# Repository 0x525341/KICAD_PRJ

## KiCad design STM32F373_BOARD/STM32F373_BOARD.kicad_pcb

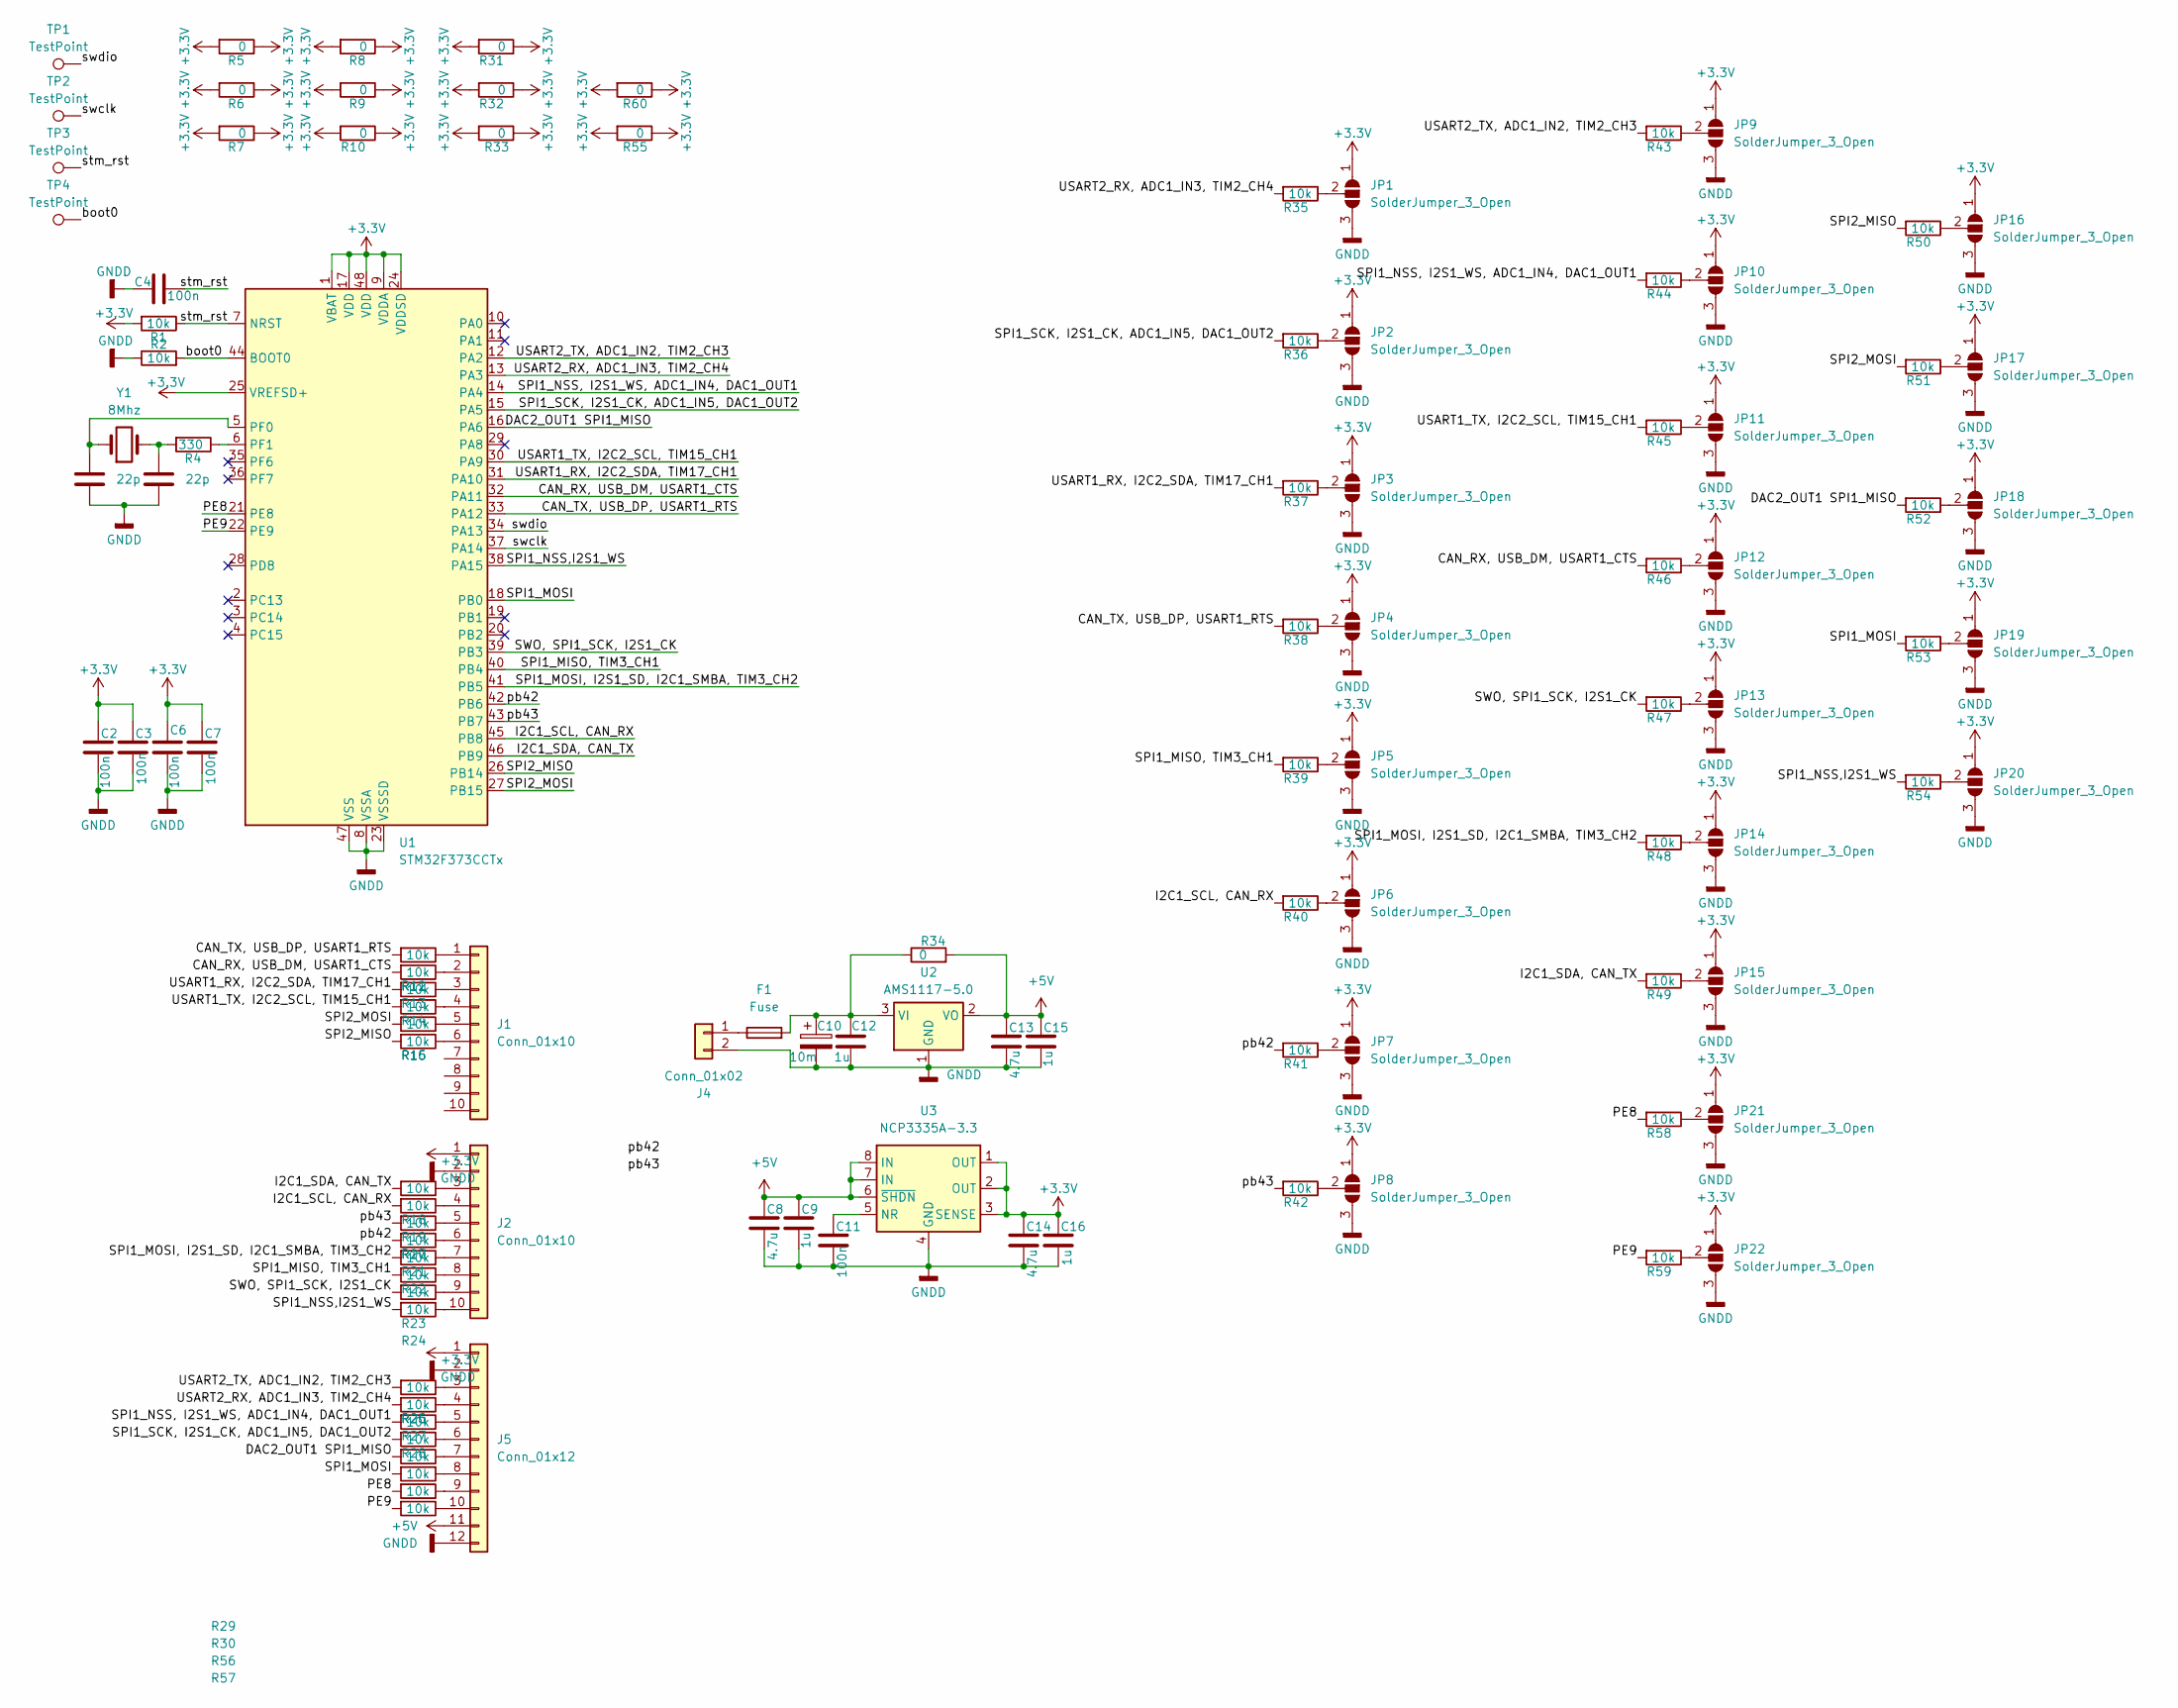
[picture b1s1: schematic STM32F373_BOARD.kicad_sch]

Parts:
C1, C5: 22p; C_0805_2012Metric
C2, C3, C4, C6, C7, C11: 100n; C_0805_2012Metric
C8, C13, C14: 4.7u; C_1206_3216Metric
C9, C12, C15, C16: 1u; C_1206_3216Metric
C10: 10m; CP_EIA-7343-31_Kemet-D_HandSolder
F1: Fuse; Fuse_1210_3225Metric_Pad1.42x2.65mm_HandSolder
J1, J2: Conn_01x10; PinHeader_1x10_P2.54mm_Vertical_SMD_Pin1Right
J4: Conn_01x02; PinSocket_1x02_P2.54mm_Vertical_SMD_Pin1Right
J5: Conn_01x12; PinHeader_1x12_P2.54mm_Vertical_SMD_Pin1Left
JP1, JP2, JP3, JP4, JP5, JP6, JP7, JP8, JP9, JP10, JP11, JP12, JP13, JP14, JP15, JP16, JP17, JP18, JP19, JP20, JP21, JP22: SolderJumper_3_Open; SolderJumper-3_P1.3mm_Open_RoundedPad1.0x1.5mm
R1: 10k; R_0805_2012Metric
R2, R11, R12, R13, R14, R15, R16, R17, R18, R19, R20, R21, R22, R23, R24, R25, R26, R27, R28, R29, R30, R35, R36, R37, R38, R39, R40, R41, R42, R43, R44, R45, R46, R47, R48, R49, R50, R51, R52, R53, R54, R56, R57, R58, R59: 10k; R_1206_3216Metric
R4: 330; R_0805_2012Metric
R5, R6, R7, R8, R9, R10, R31, R32, R33, R55, R60: 0; R_0805_2012Metric
R34: 0; R_1206_3216Metric
TP1, TP2, TP3, TP4: TestPoint; TestPoint_Pad_1.5x1.5mm
U1: STM32F373CCTx; LQFP-48_7x7mm_P0.5mm
U2: AMS1117-5.0; SOT-223-3_TabPin2
U3: NCP3335A-3.3; MSOP-8_3x3mm_P0.65mm
Y1: 8Mhz; Crystal_SMD_0603-2Pin_6.0x3.5mm

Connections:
+3.3V: C2.1, C3.1, C6.1, C7.1, C14.1, C16.1, J2.1, J5.1, JP1.1 (A), JP2.1 (A), JP3.1 (A), JP4.1 (A), JP5.1 (A), JP6.1 (A), JP7.1 (A), JP8.1 (A), JP9.1 (A), JP10.1 (A), JP11.1 (A), JP12.1 (A), JP13.1 (A), JP14.1 (A), JP15.1 (A), JP16.1 (A), JP17.1 (A), JP18.1 (A), JP19.1 (A), JP20.1 (A), JP21.1 (A), JP22.1 (A), R1.2, R5.1, R5.2, R6.1, R6.2, R7.1, R7.2, R8.1, R8.2, R9.1, R9.2, R10.1, R10.2, R31.1, R31.2, R32.1, R32.2, R33.1, R33.2, R55.1, R55.2, R60.1, R60.2, U1.1 (VBAT), U1.9 (VDDA), U1.17 (VDD), U1.24 (VDDSD), U1.25 (VREFSD+), U1.48 (VDD), U3.1 (OUT), U3.2 (OUT), U3.3 (SENSE)
+5V: C8.1, C9.1, C13.1, C15.1, J5.11, R34.2, U2.2 (VO), U3.6 (~SHDN), U3.7 (IN), U3.8 (IN)
/CAN_RX, USB_DM, USART1_CTS: R12.2, R46.2, U1.32 (PA11)
/CAN_TX, USB_DP, USART1_RTS: R11.2, R38.2, U1.33 (PA12)
/DAC2_OUT1 SPI1_MISO: R29.2, R52.2, U1.16 (PA6)
/I2C1_SCL, CAN_RX: R18.2, R40.2, U1.45 (PB8)
/I2C1_SDA, CAN_TX: R17.2, R49.2, U1.46 (PB9)
/PE8: R56.2, R58.2, U1.21 (PE8)
/PE9: R57.2, R59.2, U1.22 (PE9)
/SPI1_MISO, TIM3_CH1: R22.2, R39.2, U1.40 (PB4)
/SPI1_MOSI: R30.2, R53.2, U1.18 (PB0)
/SPI1_MOSI, I2S1_SD, I2C1_SMBA, TIM3_CH2: R21.2, R48.2, U1.41 (PB5)
/SPI1_NSS, I2S1_WS, ADC1_IN4, DAC1_OUT1: R27.2, R44.2, U1.14 (PA4)
/SPI1_NSS,I2S1_WS: R24.2, R54.2, U1.38 (PA15)
/SPI1_SCK, I2S1_CK, ADC1_IN5, DAC1_OUT2: R28.2, R36.2, U1.15 (PA5)
/SPI2_MISO: R16.2, R50.2, U1.26 (PB14)
/SPI2_MOSI: R15.2, R51.2, U1.27 (PB15)
/SWO, SPI1_SCK, I2S1_CK: R23.2, R47.2, U1.39 (PB3)
/USART1_RX, I2C2_SDA, TIM17_CH1: R13.2, R37.2, U1.31 (PA10)
/USART1_TX, I2C2_SCL, TIM15_CH1: R14.2, R45.2, U1.30 (PA9)
/USART2_RX, ADC1_IN3, TIM2_CH4: R26.2, R35.2, U1.13 (PA3)
/USART2_TX, ADC1_IN2, TIM2_CH3: R25.2, R43.2, U1.12 (PA2)
/boot0: R2.2, TP4.1 (1_1), U1.44 (BOOT0)
/pb42: R20.2, R41.2, U1.42 (PB6)
/pb43: R19.2, R42.2, U1.43 (PB7)
/stm_rst: C4.2, R1.1, TP3.1 (1_1), U1.7 (NRST)
/swclk: TP2.1 (1_1), U1.37 (PA14)
/swdio: TP1.1 (1_1), U1.34 (PA13)
GNDD: C1.2, C2.2, C3.2, C4.1, C5.2, C6.2, C7.2, C8.2, C9.2, C10.2, C11.2, C12.2, C13.2, C14.2, C15.2, C16.2, J2.2, J4.2, J5.2, J5.12, JP1.3 (B), JP2.3 (B), JP3.3 (B), JP4.3 (B), JP5.3 (B), JP6.3 (B), JP7.3 (B), JP8.3 (B), JP9.3 (B), JP10.3 (B), JP11.3 (B), JP12.3 (B), JP13.3 (B), JP14.3 (B), JP15.3 (B), JP16.3 (B), JP17.3 (B), JP18.3 (B), JP19.3 (B), JP20.3 (B), JP21.3 (B), JP22.3 (B), R2.1, U1.8 (VSSA), U1.23 (VSSSD), U1.47 (VSS), U2.1 (GND), U3.4 (GND)
unnamed: C5.1, R4.2, Y1.2
unnamed: J1.1, R11.1
unnamed: J1.2, R12.1
unnamed: J1.3, R13.1
unnamed: J1.4, R14.1
unnamed: J1.5, R15.1
unnamed: J1.6, R16.1
unnamed: J2.3, R17.1
unnamed: J2.4, R18.1
unnamed: J2.5, R19.1
unnamed: J2.6, R20.1
unnamed: J2.7, R21.1
unnamed: J2.8, R22.1
unnamed: J2.9, R23.1
unnamed: J2.10, R24.1
unnamed: F1.1, J4.1
unnamed: J5.3, R25.1
unnamed: J5.4, R26.1
unnamed: J5.5, R27.1
unnamed: J5.6, R28.1
unnamed: J5.7, R29.1
unnamed: J5.8, R30.1
unnamed: J5.9, R56.1
unnamed: J5.10, R57.1
unnamed: JP1.2 (C), R35.1
unnamed: JP2.2 (C), R36.1
unnamed: JP3.2 (C), R37.1
unnamed: JP4.2 (C), R38.1
unnamed: JP5.2 (C), R39.1
unnamed: JP6.2 (C), R40.1
unnamed: JP7.2 (C), R41.1
unnamed: JP8.2 (C), R42.1
unnamed: JP9.2 (C), R43.1
unnamed: JP10.2 (C), R44.1
unnamed: JP11.2 (C), R45.1
unnamed: JP12.2 (C), R46.1
unnamed: JP13.2 (C), R47.1
unnamed: JP14.2 (C), R48.1
unnamed: JP15.2 (C), R49.1
unnamed: JP16.2 (C), R50.1
unnamed: JP17.2 (C), R51.1
unnamed: JP18.2 (C), R52.1
unnamed: JP19.2 (C), R53.1
unnamed: JP20.2 (C), R54.1
unnamed: JP21.2 (C), R58.1
unnamed: JP22.2 (C), R59.1
unnamed: C1.1, U1.5 (PF0), Y1.1
unnamed: R4.1, U1.6 (PF1)
unnamed: C10.1, C12.1, F1.2, R34.1, U2.3 (VI)
unnamed: C11.1, U3.5 (NR)

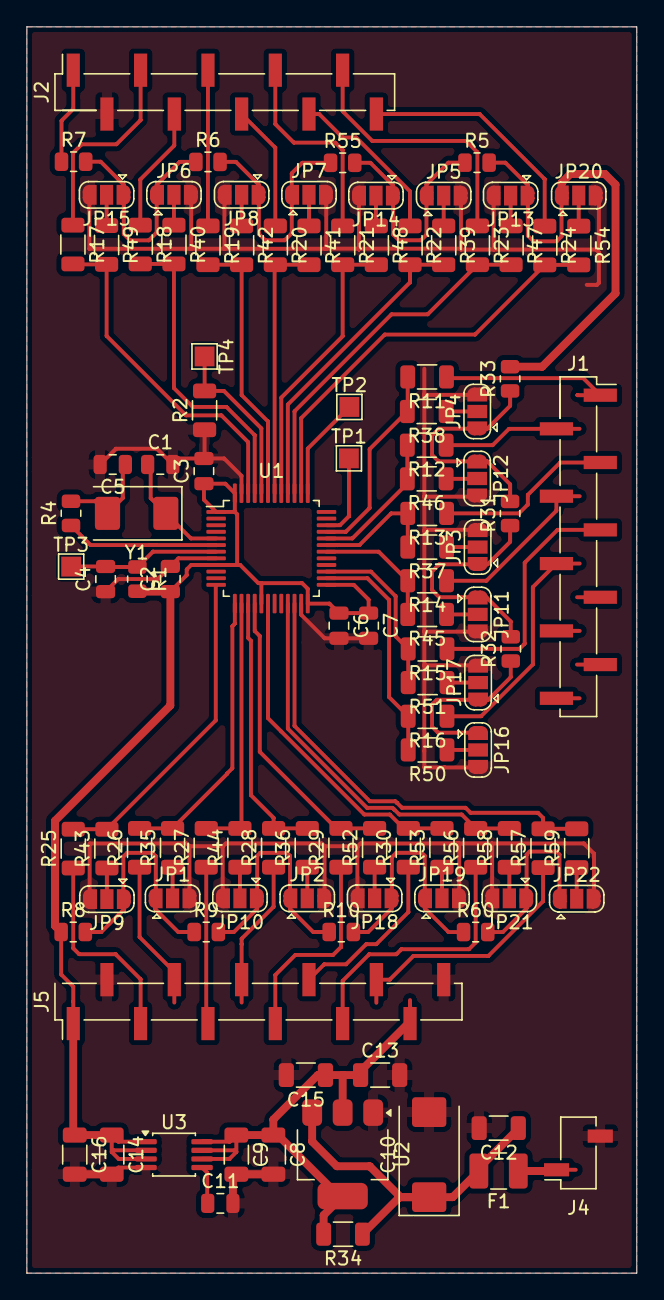
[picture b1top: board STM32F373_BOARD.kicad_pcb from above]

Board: 2 copper layers, 46.0 x 94.0 mm, 110 parts (0 on the bottom side), 79 nets.

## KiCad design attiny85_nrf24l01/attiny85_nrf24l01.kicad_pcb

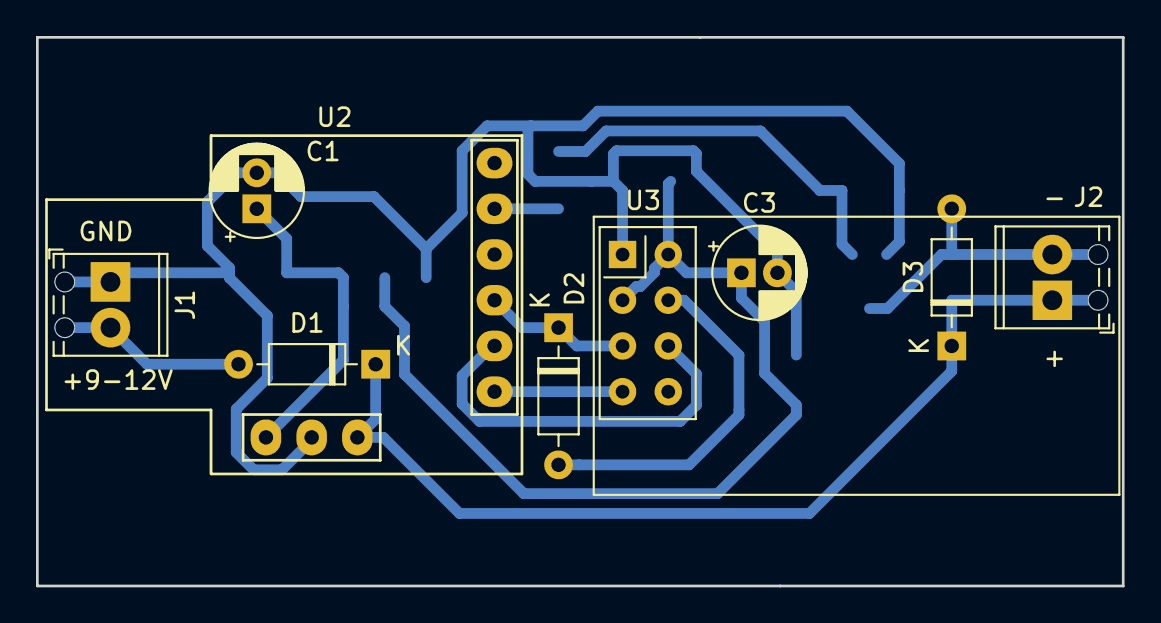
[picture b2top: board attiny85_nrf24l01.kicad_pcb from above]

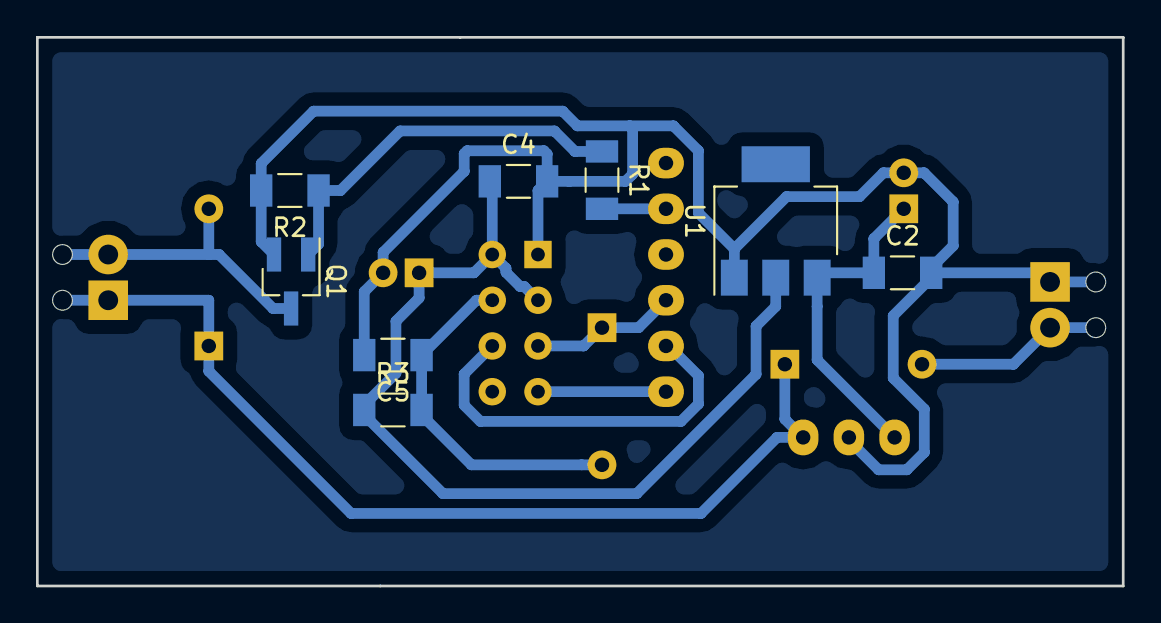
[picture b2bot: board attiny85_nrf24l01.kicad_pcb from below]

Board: 2 copper layers, 60.3 x 30.5 mm, 17 parts (8 on the bottom side), 12 nets.

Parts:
C1, C3: 10mkF; CP_Radial_D5.0mm_P2.00mm
C2, C4: 0,1mkF; C_1206_3216Metric_Pad1.24x1.80mm_HandSolder
C5: 10/100nF; C_1206_3216Metric_Pad1.24x1.80mm_HandSolder
D1: 1N5819; D_DO-35_SOD27_P7.62mm_Horizontal
D2: 4148; D_DO-35_SOD27_P7.62mm_Horizontal
D3: 1N4007; D_DO-35_SOD27_P7.62mm_Horizontal
J1: POWER; TerminalBlock_Phoenix_MPT-0,5-2-2.54_1x02_P2.54mm_Horizontal
J2: VALVE; TerminalBlock_Phoenix_MPT-0,5-2-2.54_1x02_P2.54mm_Horizontal
Q1: IRLML2502TRPBF; SOT-23_Handsoldering
R1: 100Om; R_1206_3216Metric_Pad1.24x1.80mm_HandSolder
R2: 10kOm; R_1206_3216Metric_Pad1.24x1.80mm_HandSolder
R3: 1/22kOm; R_1206_3216Metric_Pad1.24x1.80mm_HandSolder
U1: LT1117-3.3; SOT-223
U2: DIGISPARK; Shield_Digispark
U3: NRF24L01_Breakout; nRF24L01_Breakout

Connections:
+9V: D1.1, D3.1, J2.1, U2.8
+BATT: D1.2, J1.2
-BATT: C1.2, C2.2, C3.2, C4.2, C5.2, J1.1, Q1.2, R2.2, U1.1, U2.4, U3.1
/+3,3V: C3.1, C4.1, R3.1, U1.2, U3.2, U3.3
/+5V: C1.1, C2.1, U1.3, U2.9
/CONTROL_VALVE: R1.2, U2.3
unnamed: C5.1, D2.2, R3.2, U3.4
unnamed: D2.1, U2.7, U3.5
unnamed: D3.2, J2.2, Q1.3
unnamed: Q1.1, R1.1, R2.1
unnamed: U2.5, U3.7
unnamed: U2.6, U3.6

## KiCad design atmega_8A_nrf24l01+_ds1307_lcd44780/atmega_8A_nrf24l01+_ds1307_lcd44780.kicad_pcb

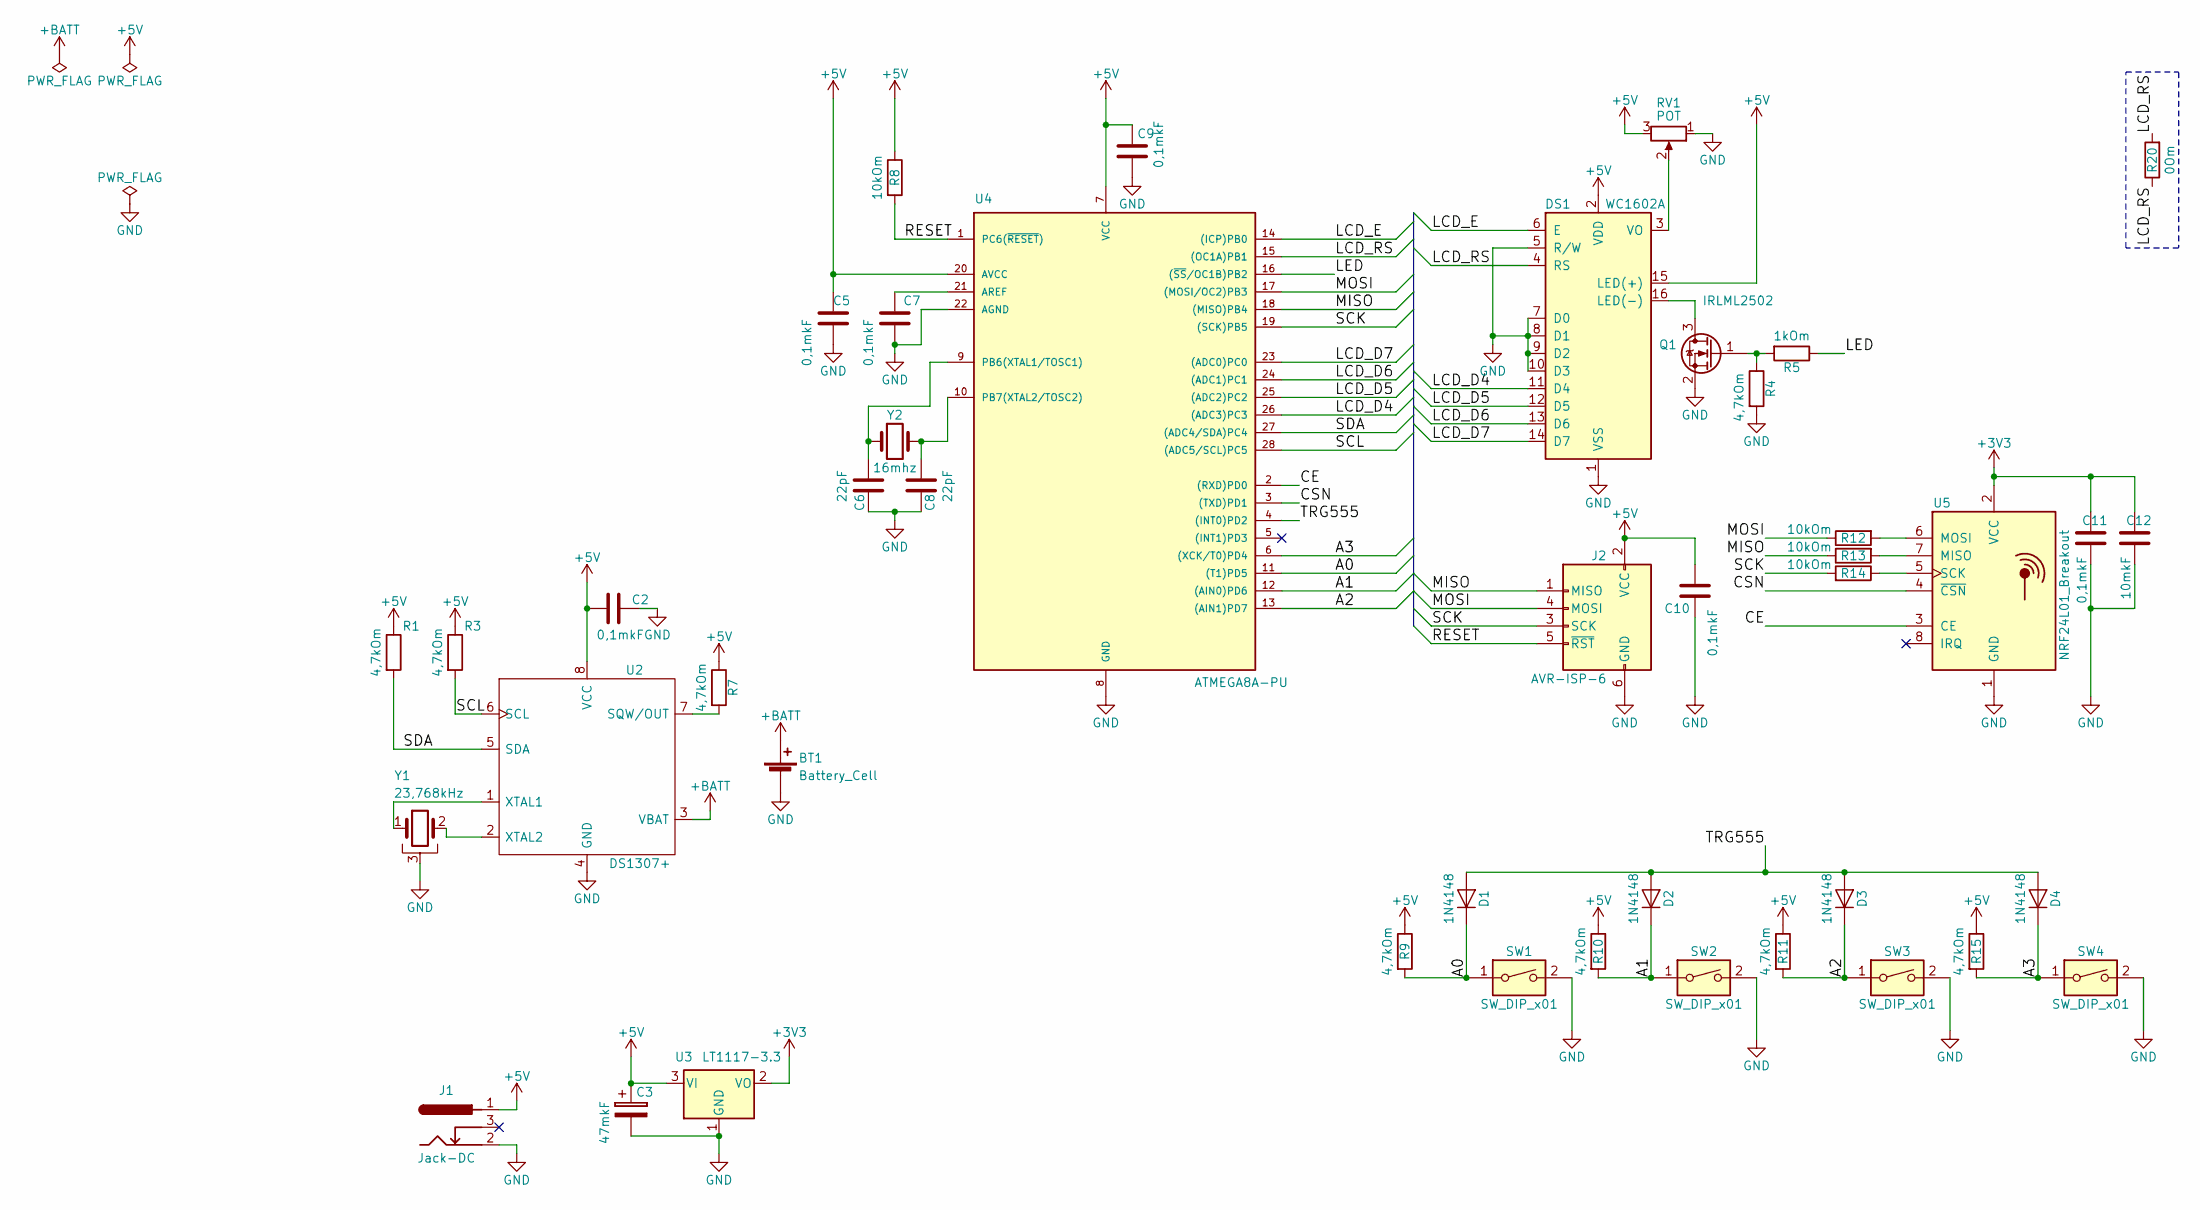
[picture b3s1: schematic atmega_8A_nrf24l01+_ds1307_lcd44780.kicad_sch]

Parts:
BT1: Battery_Cell; BatteryHolder_CR2032H
C2, C5, C7, C9, C10, C11: 0,1mkF; C_1206_3216Metric_Pad1.24x1.80mm_HandSolder
C3: 47mkF; CP_Radial_D5.0mm_P2.00mm
C6, C8: 22pF; C_1206_3216Metric_Pad1.24x1.80mm_HandSolder
C12: 10mkF; C_1206_3216Metric_Pad1.24x1.80mm_HandSolder
D1, D2, D3, D4: 1N4148; D_DO-35_SOD27_P7.62mm_Horizontal
DS1: WC1602A
J1: Jack-DC; ds-313
J2: AVR-ISP-6; PinHeader_2x03_P2.54mm_Vertical
Q1: IRLML2502; SOT-23_Handsoldering
R1, R3, R4, R7, R9, R10, R11, R15: 4,7kOm; R_1206_3216Metric_Pad1.24x1.80mm_HandSolder
R5: 1kOm; R_1206_3216Metric_Pad1.24x1.80mm_HandSolder
R8, R12, R13, R14: 10kOm; R_1206_3216Metric_Pad1.24x1.80mm_HandSolder
R20: 0Om; R_1206_3216Metric_Pad1.24x1.80mm_HandSolder
RV1: POT; Potentiometer_ACP_CA9-H5_Horizontal
SW1, SW2, SW3, SW4: SW_DIP_x01; SW_PUSH_6mm
U2: DS1307+; SOIC-8_3.9x4.9mm_P1.27mm
U3: LT1117-3.3; SOT-223-3_TabPin2
U4: ATMEGA8A-PU; DIP-28_W7.62mm_LongPads
U5: NRF24L01_Breakout; nRF24L01_Breakout
Y1: 23,768kHz; Crystal_AT310_D3.0mm_L10.0mm_Horizontal_1EP_style2
Y2: 16mhz; Crystal_HC49-4H_Vertical

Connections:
+3V3: C11.2, C12.2, U3.2 (VO), U5.2 (VCC)
+5V: C2.2, C3.1, C5.2, C9.1, C10.2, DS1.2 (VDD), DS1.15 (LED(+)), J1.1, J2.2 (VCC), R1.1, R3.1, R7.1, R8.1, R9.1, R10.1, R11.1, R15.1, RV1.3, U2.8 (VCC), U3.3 (VI), U4.7 (VCC), U4.20 (AVCC)
+BATT: BT1.1 (+), U2.3 (VBAT)
/A0: D1.1 (K), R9.2, SW1.1, U4.11 ((T1)PD5)
/A1: D2.1 (K), R10.2, SW2.1, U4.12 ((AIN0)PD6)
/A2: D3.1 (K), R11.2, SW3.1, U4.13 ((AIN1)PD7)
/A3: D4.1 (K), R15.2, SW4.1, U4.6 ((XCK/T0)PD4)
/CE: U4.2 ((RXD)PD0), U5.3 (CE)
/CSN: U4.3 ((TXD)PD1), U5.4 (~CSN)
/LCD_D4: DS1.11 (D4), U4.26 ((ADC3)PC3)
/LCD_D5: DS1.12 (D5), U4.25 ((ADC2)PC2)
/LCD_D6: DS1.13 (D6), U4.24 ((ADC1)PC1)
/LCD_D7: DS1.14 (D7), U4.23 ((ADC0)PC0)
/LCD_E: DS1.6 (E), U4.14 ((ICP)PB0)
/LCD_RS: DS1.4 (RS), R20.1, R20.2, U4.15 ((OC1A)PB1)
/LED: R5.1, U4.16 ((~SS/OC1B)PB2)
/MISO: J2.1 (MISO), R13.1, U4.18 ((MISO)PB4)
/MOSI: J2.4 (MOSI), R12.1, U4.17 ((MOSI/OC2)PB3)
/RESET: J2.5 (~RST), R8.2, U4.1 (PC6(~RESET))
/SCK: J2.3 (SCK), R14.2, U4.19 ((SCK)PB5)
/SCL: R3.2, U2.6 (SCL), U4.28 ((ADC5/SCL)PC5)
/SDA: R1.2, U2.5 (SDA), U4.27 ((ADC4/SDA)PC4)
/TRG555: D1.2 (A), D2.2 (A), D3.2 (A), D4.2 (A), U4.4 ((INT0)PD2)
GND: BT1.2 (-), C2.1, C3.2, C5.1, C6.2, C7.1, C8.2, C9.2, C10.1, C11.1, C12.1, DS1.1 (VSS), DS1.5 (R/W), DS1.7 (D0), DS1.8 (D1), DS1.9 (D2), DS1.10 (D3), J1.2, J2.6 (GND), Q1.2 (S), R4.2, RV1.1, SW1.2, SW2.2, SW3.2, SW4.2, U2.4 (GND), U3.1 (GND), U4.8 (GND), U4.22 (AGND), U5.1 (GND), Y1.3
unnamed: C6.1, U4.9 (PB6(XTAL1/TOSC1)), Y2.1
unnamed: C7.2, U4.21 (AREF)
unnamed: C8.1, U4.10 (PB7(XTAL2/TOSC2)), Y2.2
unnamed: DS1.3 (VO), RV1.2
unnamed: DS1.16 (LED(-)), Q1.3 (D)
unnamed: Q1.1 (G), R4.1, R5.2
unnamed: R7.2, U2.7 (SQW/OUT)
unnamed: R12.2, U5.6 (MOSI)
unnamed: R13.2, U5.7 (MISO)
unnamed: R14.1, U5.5 (SCK)
unnamed: U2.1 (XTAL1), Y1.1
unnamed: U2.2 (XTAL2), Y1.2

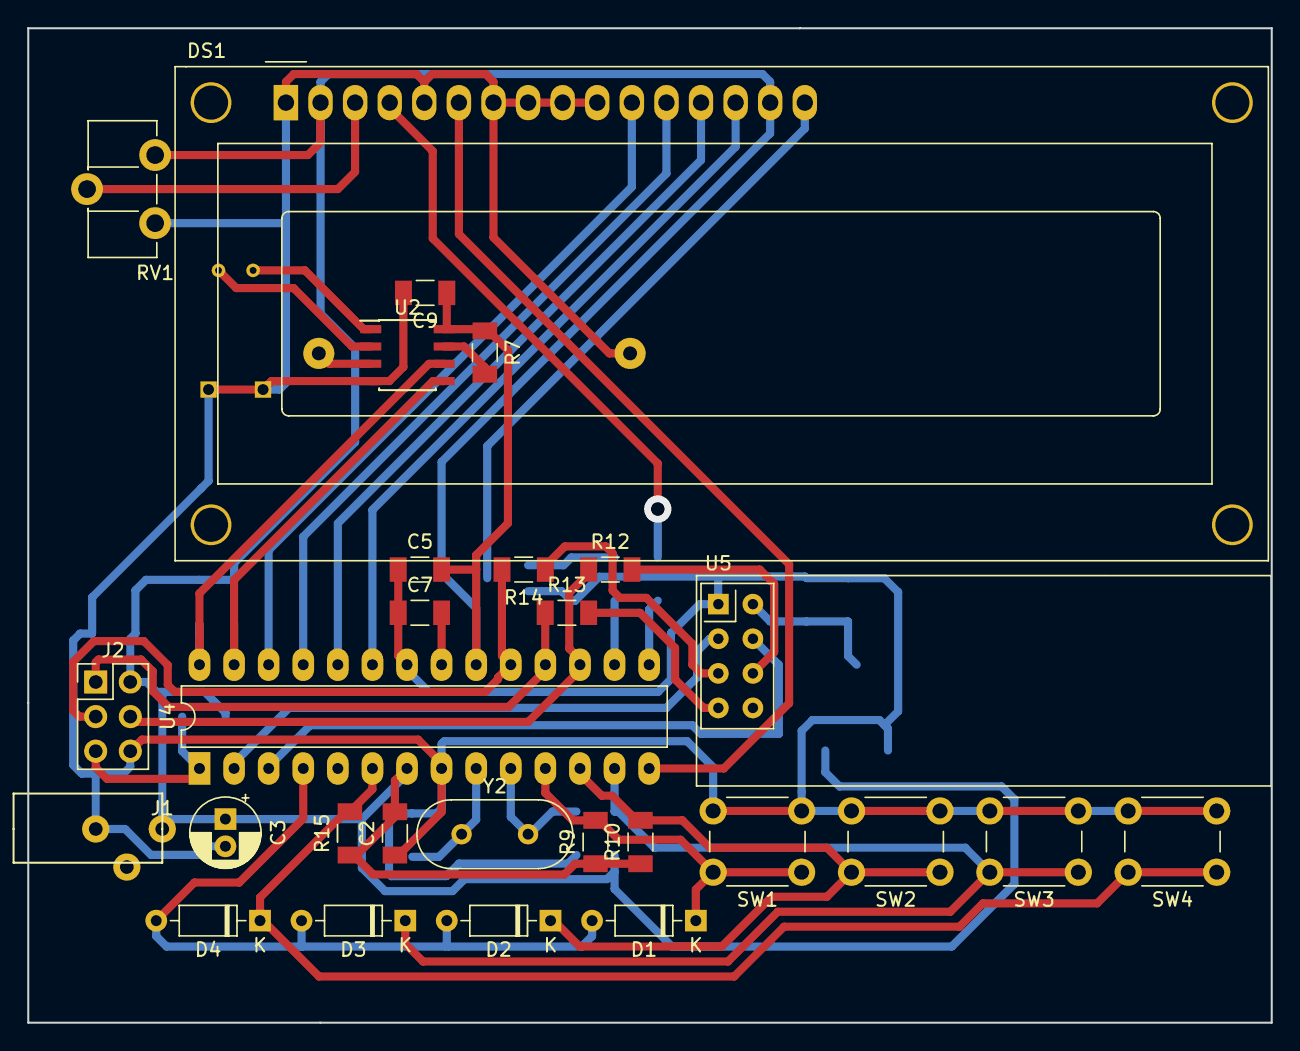
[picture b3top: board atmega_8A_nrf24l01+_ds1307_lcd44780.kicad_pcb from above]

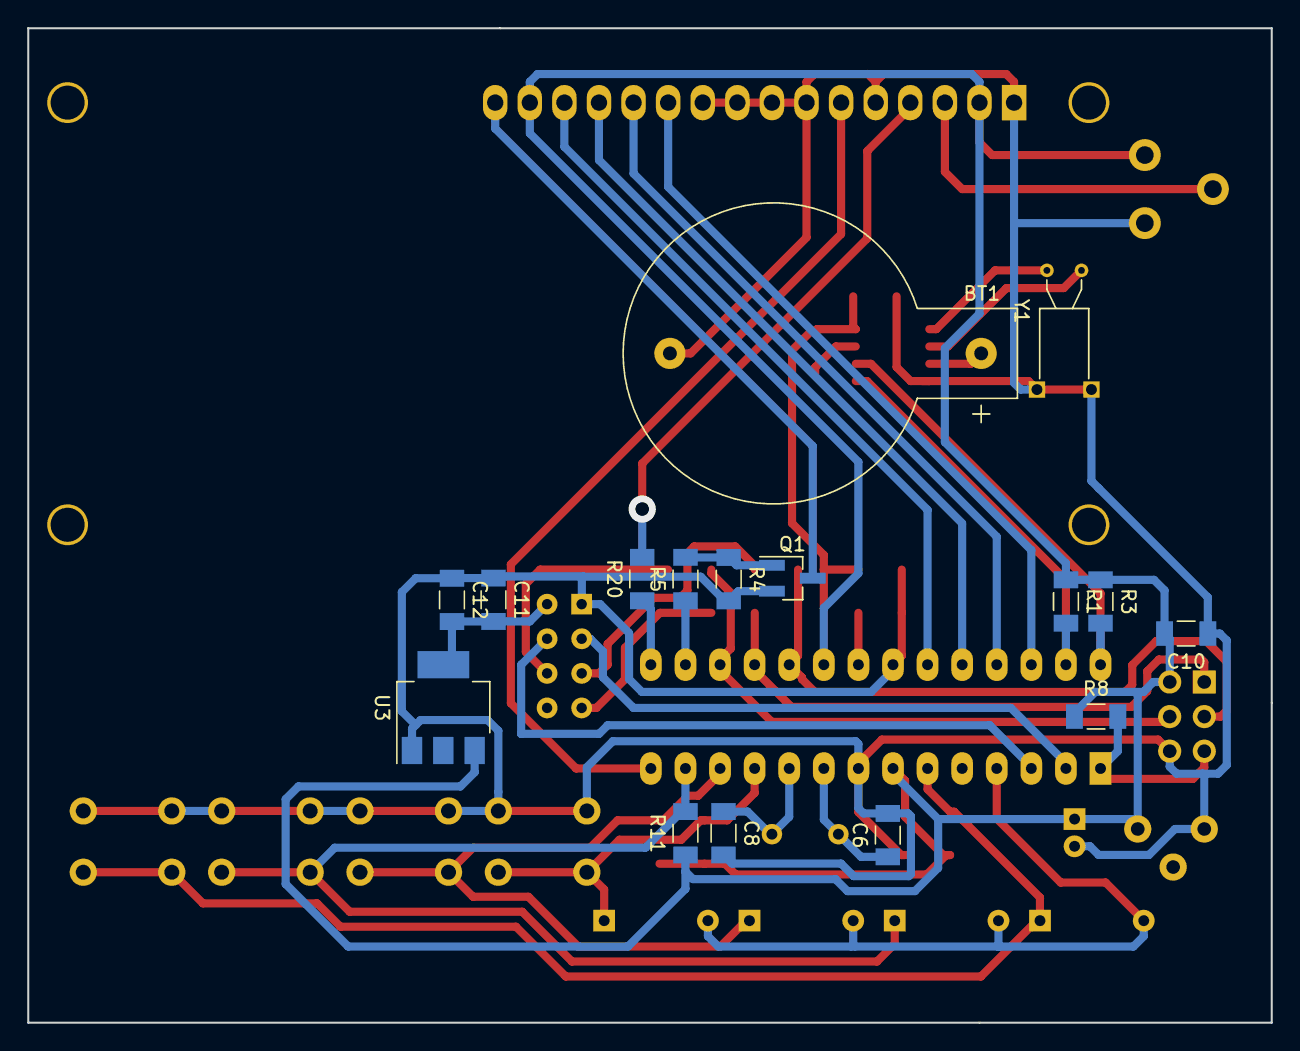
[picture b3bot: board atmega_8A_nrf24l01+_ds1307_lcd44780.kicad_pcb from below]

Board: 2 copper layers, 91.3 x 73.0 mm, 44 parts (16 on the bottom side), 36 nets.

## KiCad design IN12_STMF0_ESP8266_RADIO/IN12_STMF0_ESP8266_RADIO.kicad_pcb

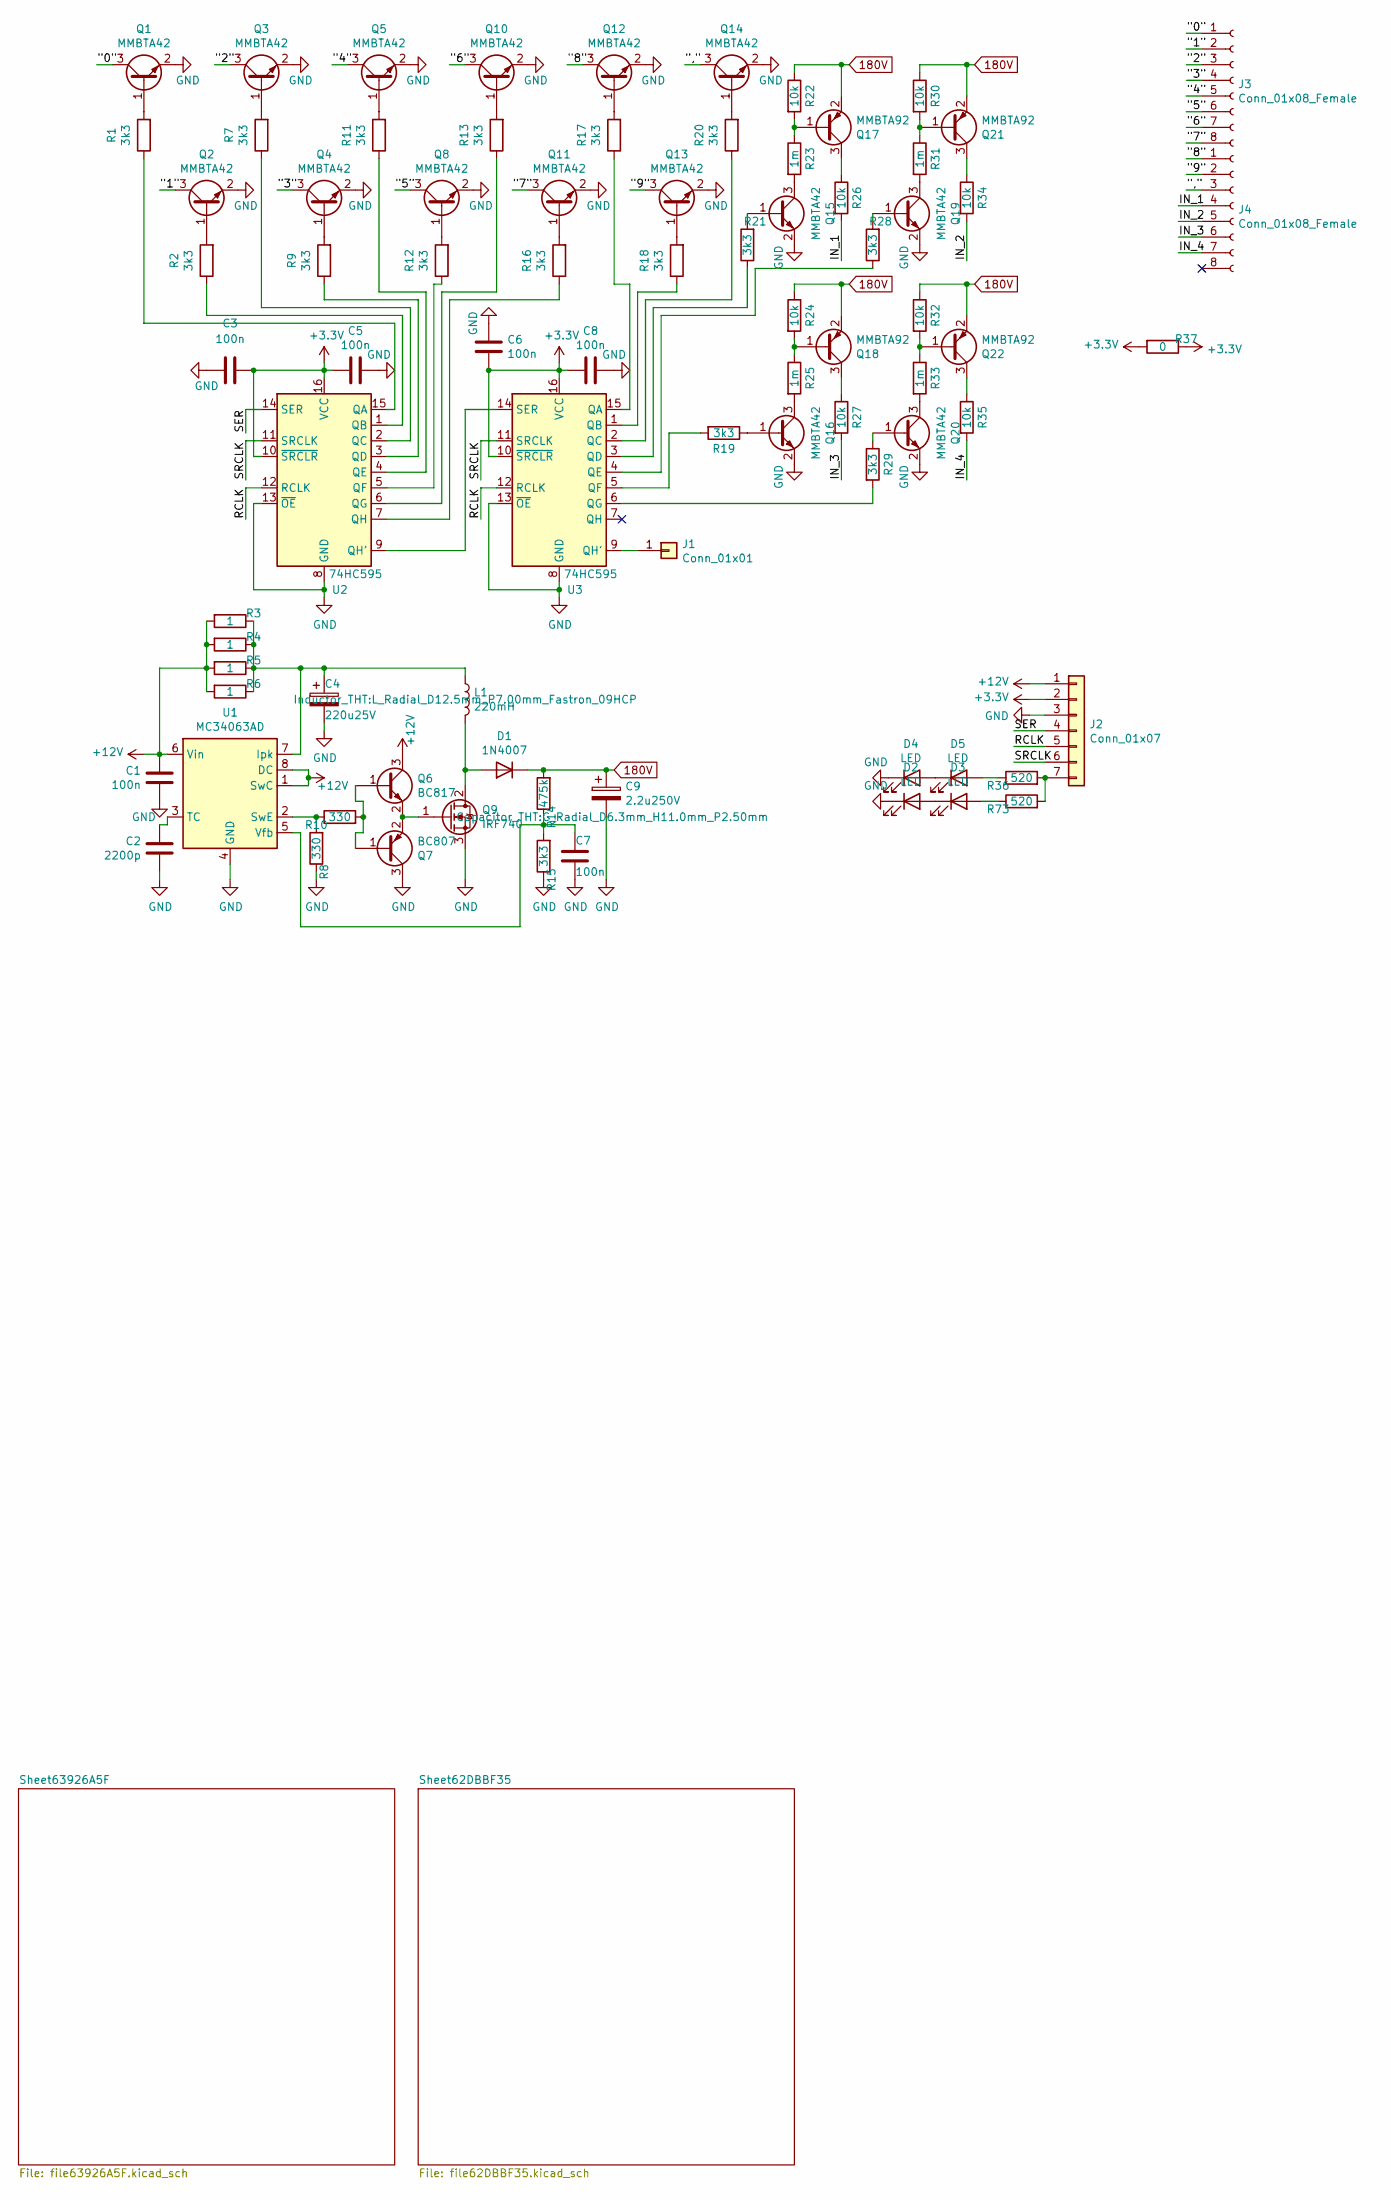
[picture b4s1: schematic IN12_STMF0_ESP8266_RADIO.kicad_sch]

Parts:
C1, C3, C5, C6, C7, C8: 100n; C_1206_3216Metric
C2: 2200p; C_1206_3216Metric
C4: 220u25V; CP_Radial_D8.0mm_P3.50mm
C9: 2.2u250V; C_Radial_D6.3mm_H11.0mm_P2.50mm
D1: 1N4007; D_DO-41_SOD81_P10.16mm_Horizontal
D2, D3, D4, D5: LED; LED_1206_3216Metric
J1: Conn_01x01; PinHeader_1x01_P2.54mm_Vertical
J2: Conn_01x07; PinHeader_1x07_P2.54mm_Vertical
J3, J4: Conn_01x08_Female; PinSocket_1x08_P2.54mm_Vertical
L1: 220mH; L_Radial_D12.5mm_P7.00mm_Fastron_09HCP
Q1, Q2, Q3, Q4, Q5, Q8, Q10, Q11, Q12, Q13, Q14, Q15, Q16, Q19, Q20: MMBTA42; SOT-23
Q6: BC817; SOT-23
Q7: BC807; SOT-23
Q9: IRF740; TO-263-2
Q17, Q18, Q21, Q22: MMBTA92; SOT-23
R1, R2, R7, R9, R11, R12, R13, R15, R16, R17, R18, R19, R20, R21, R28, R29: 3k3; R_1206_3216Metric
R3, R4, R5, R6: 1; R_1206_3216Metric
R8, R10: 330; R_1206_3216Metric
R14: 475k; R_1206_3216Metric
R22, R24, R26, R27, R30, R32, R34, R35: 10k; R_1206_3216Metric
R23, R25, R31, R33: 1m; R_1206_3216Metric
R36, R73: 520; R_1206_3216Metric
R37: 0; R_1206_3216Metric
U1: MC34063AD; SOIC-8_3.9x4.9mm_P1.27mm
U2, U3: 74HC595; DIP-16_W7.62mm

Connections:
180V: C9.1, D1.1 (K), Q17.2 (E), Q18.2 (E), Q21.2 (E), Q22.2 (E), R14.2, R22.1, R24.1, R30.1, R32.1
+3V3: C3.1, C5.1, C6.1, C8.1, J2.2, R37.1, R37.2, U2.10 (~SRCLR), U2.16 (VCC), U3.10 (~SRCLR), U3.16 (VCC); also elsewhere on the board
+12V: C1.2, J2.1, Q6.3 (C), R3.2, R4.2, R5.2, R6.2, U1.1 (SwC), U1.6 (Vin), U1.8 (DC); also elsewhere on the board
/"0": J3.1, Q1.3 (C)
/"1": J3.2, Q2.3 (C)
/"2": J3.3, Q3.3 (C)
/"3": J3.4, Q4.3 (C)
/"4": J3.5, Q5.3 (C)
/"5": J3.6, Q8.3 (C)
/"6": J3.7, Q10.3 (C)
/"7": J3.8, Q11.3 (C)
/"8": J4.1, Q12.3 (C)
/"9": J4.2, Q13.3 (C)
/",": J4.3, Q14.3 (C)
/IN_1: J4.4, R26.2
/IN_2: J4.5, R34.2
/IN_3: J4.6, R27.2
/IN_4: J4.7, R35.2
/RCLK: J2.5, U2.12 (RCLK), U3.12 (RCLK)
/SER: J2.4, U2.14 (SER)
/SRCLK: J2.6, U2.11 (SRCLK), U3.11 (SRCLK)
unnamed: C2.1, U1.3 (TC)
unnamed: C4.1, L1.1, R3.1, R4.1, R5.1, R6.1, U1.7 (Ipk)
unnamed: C7.1, R14.1, R15.2, U1.5 (Vfb)
unnamed: D1.2 (A), L1.2, Q9.2 (D)
unnamed: D2.2 (A), D3.1 (K)
unnamed: D4.2 (A), D5.1 (K)
unnamed: D5.2 (A), R36.1
unnamed: J1.1, U3.9 (QH')
unnamed: J2.7, R36.2, R73.2
unnamed: Q1.1 (B), R1.2
unnamed: Q2.1 (B), R2.2
unnamed: Q3.1 (B), R7.2
unnamed: Q4.1 (B), R9.2
unnamed: Q5.1 (B), R11.2
unnamed: Q6.1 (B), Q7.1 (B), R10.2
unnamed: Q6.2 (E), Q7.2 (E), Q9.1 (G)
unnamed: Q8.1 (B), R12.2
unnamed: Q10.1 (B), R13.2
unnamed: Q11.1 (B), R16.2
unnamed: Q12.1 (B), R17.2
unnamed: Q13.1 (B), R18.2
unnamed: Q14.1 (B), R20.2
unnamed: Q15.1 (B), R21.2
unnamed: Q15.3 (C), R23.2
unnamed: Q16.1 (B), R19.1
unnamed: Q16.3 (C), R25.2
unnamed: Q17.1 (B), R22.2, R23.1
unnamed: Q17.3 (C), R26.1
unnamed: Q18.1 (B), R24.2, R25.1
unnamed: Q18.3 (C), R27.1
unnamed: Q19.1 (B), R28.2
unnamed: Q19.3 (C), R31.2
unnamed: Q20.1 (B), R29.1
unnamed: Q20.3 (C), R33.2
unnamed: Q21.1 (B), R30.2, R31.1
unnamed: Q21.3 (C), R34.1
unnamed: Q22.1 (B), R32.2, R33.1
unnamed: Q22.3 (C), R35.1
unnamed: R1.1, U2.15 (QA)
unnamed: R2.1, U2.1 (QB)
unnamed: R7.1, U2.2 (QC)
unnamed: R9.1, U2.3 (QD)
unnamed: R8.2, R10.1, U1.2 (SwE)
unnamed: R11.1, U2.4 (QE)
unnamed: R12.1, U2.5 (QF)
unnamed: R13.1, U2.6 (QG)
unnamed: R16.1, U2.7 (QH)
unnamed: R17.1, U3.15 (QA)
unnamed: R18.1, U3.1 (QB)
unnamed: R19.2, U3.5 (QF)
unnamed: R20.1, U3.2 (QC)
unnamed: R21.1, U3.3 (QD)
unnamed: R28.1, U3.4 (QE)
unnamed: R29.2, U3.6 (QG)
unnamed: U2.9 (QH'), U3.14 (SER)
